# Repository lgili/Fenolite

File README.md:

# Fenolite

**PCB automation in Python, for engineers and AI agents.**

Create PCB projects from code, inspect KiCad and Altium files, and review designs in your browser.
Use the Python library or a CLI with structured JSON results, explicit write plans and conversion loss reports.

[**Get started**](https://github.com/lgili/Fenolite/blob/main/docs/quickstart.md) ·
[Documentation](https://github.com/lgili/Fenolite/blob/main/docs/index.md) ·
[Examples](https://github.com/lgili/Fenolite/tree/main/examples) ·
[What's in 0.5](https://github.com/lgili/Fenolite/blob/main/docs/launch/v0.5.md) ·
[Get help](https://github.com/lgili/Fenolite/issues)

*Actual Fenolite viewer, using a small example authored for this project. No KiCad or Altium installation is needed to view it.*

## Install

Requires **Python 3.11+**. It installs no other package. Heavier features are optional extras.

```bash
python -m pip install fenolite
fenolite capabilities --brief --json
fenolite init blink --confirm --json
fenolite build blink/design.py --out blink/build --confirm --json
fenolite view blink/build --serve
```

Open the local address printed by the viewer. You now have a PCB and a schematic built from
`blink/design.py`, using the built-in component catalog. No external CAD libraries are needed.
These commands create a new `blink` folder; use a fresh location.

This starter is a header, resistor and LED. It is an educational example; choose parts, ratings,
placement and rules for your own circuit before manufacturing. For reviewed write plans, a standalone
HTML export and routing, follow the [quickstart](https://github.com/lgili/Fenolite/blob/main/docs/quickstart.md).

## Three ways to use Fenolite

### Review a design in your browser

Open a KiCad or Altium project, board, schematic or library. Explore layers, highlight nets,
measure geometry and navigate between documents. Export a standalone HTML page for review.

```bash
fenolite view board.kicad_pcb --serve
fenolite view Project.PrjPcb --export review.html --confirm --json
```

The animation uses Fenolite's authored Altium Blink fixture. See the
[viewer guide](https://github.com/lgili/Fenolite/blob/main/docs/viewer.md) for supported items,
3D prerequisites and rendering limits.

### Build from Python

Define components, connections, placement and copper in a versioned source file. Build a project
that can also be opened in its CAD editor. Preserve board edits on rebuild and sync placements back to source.

```python
from fenolite.dsl import Design, Net, Part, connect, mm

design = Design("led")
design.board(mm(30), mm(20))
r1 = Part("R1", "Fenolite:Resistor", footprint="Fenolite:Chip_0603", value="330")
d1 = Part("D1", "Fenolite:LED", footprint="Fenolite:Chip_0603", value="LED")
design.add(r1, d1)
connect(Net("LED_A"), r1[2], d1[1])
r1.place(mm(10), mm(10))
d1.place(mm(20), mm(10))
```

This small fragment illustrates the DSL, not a complete powered circuit. Start with the complete
[starter tutorial](https://github.com/lgili/Fenolite/blob/main/docs/quickstart.md), then explore
[authored examples](https://github.com/lgili/Fenolite/tree/main/examples) and the
[Python DSL](https://github.com/lgili/Fenolite/blob/main/docs/dsl.md).

KiCad's CLI provides ERC, DRC, zone fills and fabrication exports. Production routing uses an external
router or copper declared in the script. The built-in `direct` router is for simple demonstrations.

### Convert and compare projects

Convert between KiCad and Altium, or write a KiCad 10 project for KiCad 9. Review what was kept,
changed or lost, with a readback comparison against the source.

```bash
fenolite convert board.PcbDoc --to kicad --out converted --dry-run --json
fenolite equivalent before.kicad_pcb after.kicad_pcb --level 5 --json
```

**Conversions and Altium writes are experimental in 0.7.** Lossy conversion requires explicit consent.
Support depends on the constructs in the input; review the report and the resulting design.
Read the [conversion guide](https://github.com/lgili/Fenolite/blob/main/docs/conversion.md).

## For AI agents

The same commands return structured JSON, typed errors, evidence labels and file receipts.
A write can be previewed with `--dry-run`, then confirmed using its `--plan` identifier.

```bash
fenolite guide start --text
fenolite skill install --help
```

The package includes an agent guide and board-design practice pages. Agents can inspect parts,
query nets and geometry, build, route, check and export using the same CLI as an engineer.
See the [agent guide](https://github.com/lgili/Fenolite/blob/main/src/fenolite/agent/skill/SKILL.md)
and [CLI contract](https://github.com/lgili/Fenolite/blob/main/docs/cli-contract.md).

<details>
<summary>Full build → fabrication command loop (requires KiCad CLI)</summary>

Use a fresh folder for this complete loop. The first six lines need no external CAD tool; fill,
check, export and render require KiCad's CLI. The direct router is a demonstration router.

```fenolite-loop
fenolite capabilities --brief --json
fenolite init blink --confirm --json
fenolite build blink/design.py --out blink/build --dry-run --json
fenolite build blink/design.py --out blink/build --confirm --json
fenolite place blink/build --strategy grid --confirm --json
fenolite route blink/build --router direct --confirm --json
fenolite fill blink/build --confirm --json
fenolite check blink/build --json
fenolite export blink/build -o blink/fab --all --manifest --confirm --json
fenolite render blink/build -o blink/views --svg --png --confirm --json
```

For fabrication exports, BOM and placement tables, see [exports](https://github.com/lgili/Fenolite/blob/main/docs/exports.md)
and [assembly](https://github.com/lgili/Fenolite/blob/main/docs/assembly.md).

</details>

## Support at a glance

> **Status: version 0.7.** Python scripts build KiCad 9/10 PCB and schematic projects. The agent loop
> uses KiCad's ERC/DRC checks, the board engineering analyses and an MCP server; conversion supports
> KiCad/Altium and the older KiCad major. Altium writes, computed Altium pours and conversions are
> experimental. See the [release scope and limits](https://github.com/lgili/Fenolite/blob/main/docs/release/v0.7.md).

| Workflow | What you need | Status in 0.7 |
|---|---|---|
| Build the starter; inspect and view supported files | Python 3.11+, browser for the viewer | Shipped; format-specific rendering limits apply |
| KiCad project generation | Python; KiCad 9 or 10 to open in the editor | Shipped |
| KiCad ERC, DRC, fill and fabrication export | `kicad-cli` 9 or 10 | Shipped; engineering review still required |
| External routing | A supported router and its prerequisites | Freerouting and KiCadRoutingTools integrations |
| KiCad/Altium conversion and KiCad downgrade | Requirements vary by direction | Experimental; explicit loss report |
| Altium project generation | Python; Altium for native validation | Experimental |

Linux, macOS and Windows are supported. Optional extras include `geo` for polygon operations
and `kicad-ipc` for a live KiCad session. Since 0.6 the package includes the stdlib-only MCP server
(`fenolite mcp`), script editing and image replies described in the
[MCP documentation](https://github.com/lgili/Fenolite/blob/main/docs/mcp.md). See
[installation and prerequisites](https://github.com/lgili/Fenolite/blob/main/docs/quickstart.md).

The viewer, conversion, board panels, slots and review tools ship since 0.5; 0.6 adds the MCP server, the
board engineering tools (analyses, tidy, reuse, silkscreen, test points, DRC gates) and the Python API.
0.7 carries Altium boards through KiCad and back (rules, classes, planes, unions, fonts, computed pours), still
experimental.
Native Draftsman writing and Embedded Board Arrays remain gated. Detailed scope and deferred checks are in the
[release record](https://github.com/lgili/Fenolite/blob/main/docs/release/v0.7.md).

## Help and contribute

Trying Fenolite on a public or self-authored example? Tell us what worked and where you got stuck.
[Ask a question or report a bug](https://github.com/lgili/Fenolite/issues), including the version,
command and error output. Keep private designs and personal paths out of public reports.

For development, clone [the repository](https://github.com/lgili/Fenolite), run `uv sync --extra dev`
and read [CONTRIBUTING.md](https://github.com/lgili/Fenolite/blob/main/CONTRIBUTING.md).

## License

[Apache-2.0](https://github.com/lgili/Fenolite/blob/main/LICENSE).
Format knowledge comes from public sources under the project's
[clean-room rules](https://github.com/lgili/Fenolite/blob/main/LEGAL.md).
Results carry evidence labels; detailed claims live in the
[evidence matrix](https://github.com/lgili/Fenolite/blob/main/docs/evidence/matrix.md).

*Fenolite* is Portuguese for phenolic board material, the laminate many of us etched our first boards on.

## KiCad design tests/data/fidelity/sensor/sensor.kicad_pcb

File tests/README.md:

# tests

| Folder | What lives there | Needs |
|---|---|---|
| `unit/` | fast, hermetic tests of `fenolite` and of repository invariants | nothing |
| `consistency/` | CLI contract checks run against every registered command (change c0002) | nothing |
| `residue/` | IP residue scan over the tree and the built wheel (change c0003) | nothing; private token list optional |
| `corpus/` | tests over the fetched public corpus (`tools/corpus_fetch.py`) | `needs_corpus` |
| `kicad/` | tests that call `kicad-cli` 9.0/10.0 | `needs_kicad` |
| `libs/` | census of the official KiCad libraries (read, resolve, count; nothing committed) | `needs_libs`, `slow` |
| `data/` | small fixtures authored for Fenolite, declared in `data/MANIFEST.toml` | nothing |

Run everything that needs no external tool with `uv run pytest -q`. `make check-fast` runs the
checks and the tests of `unit/`, `residue/` and `consistency/` that need no external resource;
`make check` runs every test. Both use parallel workers (see "Parallel runs" below).

## Markers and modes

| Marker or variable | Effect |
|---|---|
| `needs_kicad`, `needs_corpus`, `needs_libs` | skip when the resource is absent |
| `FENOLITE_REQUIRE=kicad,corpus,libs` | required-resource mode: those skips become failures (CI oracle jobs) |
| `kicad_min_major(10)` | skip when the running `kicad-cli` is older (for example `pcb upgrade`, 10.0 only); never a failure, even in required-resource mode |
| `FENOLITE_HEAVY=1` | include corpus files over 20 MB |
| `FENOLITE_KICAD_CLI=/path` | use this `kicad-cli` (a missing file counts as no `kicad-cli`) |
| `KICAD10_FOOTPRINT_DIR`, `KICAD10_SYMBOL_DIR` (or `KICAD9_*`) | official library folders for `needs_libs`; they take precedence over the install |
| `FENOLITE_KICAD_INSTALL_DIR=/path` | the KiCad share folder to use instead of the default install (a missing path counts as no install) |
| `FENOLITE_CENSUS_OUT=/path/census.json` | where `tests/libs/` writes its counts (never a tracked file) |
| `FENOLITE_ALTIUM_REPOUR_DIR=/path` | the folder of a Repour run (`tools/kit_pour_c0463.py`); without it the tests of `test_altium_pour_repour_c0463.py` that need Altium's saved boards skip |

## Parallel runs

`make check`, `make check-fast` and the CI jobs run the tests on `pytest-xdist` workers
(capability ci-baseline, "Parallel test runs"). A plain `uv run pytest ...` stays serial.

| Where | Options |
|---|---|
| `make check`, `make check-fast` | `-n auto --maxprocesses 8 --dist loadfile` (`PYTEST_WORKERS`, `PYTEST_MAX_WORKERS`, `PYTEST_PARALLEL`) |
| CI `unit`, `kicad-10`, `kicad-9` | `-n auto --dist loadfile` (4 workers on the Linux runners, 3 on macOS) |
| by hand | `uv run pytest tests/kicad -q -n 8 --dist loadfile` |

Rules for tests:

- Write only below `tmp_path`. Use no fixed port and no fixed path outside the repository.
- Do not depend on a test of another file. A summary test may read what the earlier tests of its
  own file collected: `--dist loadfile` runs a file on one worker, in file order. `--dist load`
  breaks such files, so do not use it.
- Give every subprocess call that must finish a limit of 10 s or more. A short limit is only for
  a call that must time out.
- The write modes are serial. With `FENOLITE_PROBES_WRITE=1`, `FENOLITE_GOLDEN_WRITE=1`,
  `FENOLITE_CENSUS_OUT` or `FENOLITE_CHECK_EVIDENCE` set, a run with `-n` stops with a usage error
  (exit code 4): several workers would write the same file.
- Prove a change of the options with `uv run python tools/test_outcomes.py serial.xml parallel.xml`
  on the `--junitxml` files of a serial and a parallel run.

### Measurements (2026-10-04, change c0049)

Machine: 10 cores (4 performance, 6 efficiency), macOS, KiCad 10.0.6, corpus and library caches
present. The machine was never quiet: other agents ran test suites and a Docker container during
every run below (2 to 12 other pytest processes, load average 5 to 38). The times are therefore
upper bounds, and comparisons between rows are rough.

| Run | Options | Wall time | Outcomes |
|---|---|---|---|
| whole suite, before | serial | 3357 s (56 min) | 4827 passed, 24 skipped |
| `tests/kicad` | serial (part of the run above) | 1783 s | 584 passed, 10 skipped |
| `tests/kicad` | `-n 6 --dist loadfile` | 605 s | 584 passed, 10 skipped |
| `tests/kicad` | `-n 8 --dist loadfile` | 546 s | 584 passed, 10 skipped |
| `tests/kicad` | `-n 10 --dist loadfile` | 617 s | 584 passed, 10 skipped |
| `tests/kicad` | `-n 8 --dist load` | 838 s | 583 passed, 11 skipped: `test_upgraded_summary` lost the results of its file |
| `make check-fast` | `-n auto --maxprocesses 8 --dist loadfile` | 122 s (tests 101 s) | 3832 passed, 6 skipped |
| `make check`, after (rebased: 736 more tests) | `-n auto --maxprocesses 8 --dist loadfile` | 1226 s (20 min; tests 1205 s) | 5563 passed, 24 skipped |

- The cap is 8: the fastest of 6, 8 and 10, and it leaves two cores to the `kicad-cli` threads.
- With `loadfile` the longest file bounds the run. In the `tests/kicad` runs with 8 and 10 workers,
  `tests/kicad/check/test_corpus_rt.py` alone took 509 s and 611 s on its worker (412 s serial). The
  next ones are `tests/libs/test_official_resolve.py` (468 s serial), `tests/libs/test_official_read.py`
  (411 s) and `tests/kicad/check/test_check_demos.py` (364 s). Splitting them is later work.
- Equality. `tools/test_outcomes.py` on the serial and the final parallel JUnit files: the 4849
  test ids present in both runs have the same outcome (0 differences). The parallel run has 738
  more ids (723 from changes merged between the two runs, 15 from this change) and lacks 2 that
  were renamed. On one commit, the 594 ids of `tests/kicad` (`-n 8 --dist loadfile`) equal the
  serial run id by id.
- Before and after are not the same suite: the final run holds 15 % more tests and used 4538 s of
  CPU against 3064 s. Per test, the wall time went from 0.69 s to 0.22 s (3.2 times faster) while
  other agents kept the machine at a load average of 18 to 31.
- The maintainer's earlier figure for a serial `make check` on a quiet machine was 11 minutes.

### CI effect (2026-10-04, change c0049)

The first run with the parallel steps is https://github.com/lgili/Fenolite/actions/runs/37178050484
(commit 87c4244). The last serial run that finished on `main` is https://github.com/lgili/Fenolite/actions/runs/37171749778
(commit 75f3a87); three changes landed between the two, so the suites are not the same.

| Job | Serial: job, pytest | Parallel: job, pytest | Serial outcomes | Parallel outcomes |
|---|---|---|---|---|
| `unit` (ubuntu) | 139 s, 115.82 s | 108 s, 84.14 s | 4304 passed, 1080 skipped | 4490 passed, 1109 skipped |
| `unit` (macos) | 246 s, 201.36 s | 81 s, 56.46 s | 4304 passed, 1080 skipped | 4490 passed, 1109 skipped |
| `kicad-9` | 242 s, 208.50 s | 274 s, 239.96 s | 388 passed, 340 skipped, 1 xfailed | 426 passed, 343 skipped, 1 xfailed |
| `kicad-10` | 1485 s, 1440.18 s | 1088 s, 1051.89 s | 1140 passed, 21 skipped | 1182 passed, 21 skipped |
| whole run | 1492 s (24 min 52 s) | 1095 s (18 min 15 s) | all jobs passed | all jobs passed |

- Totals. Each job grew by exactly the tests added between the two commits, counted with
  `--collect-only` on both trees: 215 for the whole suite (`unit`, 5384 to 5599), 42 for
  `tests/kicad tests/corpus` (`kicad-10`, 1161 to 1203) and 41 for `tests/kicad` (`kicad-9`, 729 to
  770). No test failed in either run.
- `kicad-9` lists every outcome (`-rA`): the 386 passed and xfailed test ids that both logs list
  have the same outcome, and the 38 ids only in the parallel log are the tests of
  `tests/kicad/copper`, added after the serial run.
- Times. `kicad-10` bounds the run: its pytest step went from 24 min 0 s to 17 min 32 s with 42 more
  tests. The design expected a drop to about a third; `--dist loadfile` is bounded by its longest
  file (see the measurements above). `kicad-9` did not get faster: 31 s more with 41 more tests.

## Audited CI partitions (c0380)

[CI profiles](../docs/ci.md) retain all five unit environments, both KiCad majors and required heavy
corpus tests at the full gate. KiCad 10 runs four whole-file partitions on separate runners. Each
partition collects the complete baseline, validates the selected execution collection and records a
terminal outcome for every selected node id. The full audit requires all fourteen receipts on the
same commit, with an exhaustive disjoint union per suite. Missing artifacts are failures, not skips.

`tools/ci_tests.py run` retains `--dist loadfile`; it does not make within-file dependencies safe for
another scheduler. Timing/JUnit artifacts show where collection, setup and test execution cost time.
`tools/test_outcomes.py` still compares legacy JUnit outcomes. The authored serial/xdist and partition
controls are `tests/unit/test_ci_execution.py`; no corpus payload is copied into those controls.
Historical timings and the pending exact-head proof are documented in `docs/ci.md`.

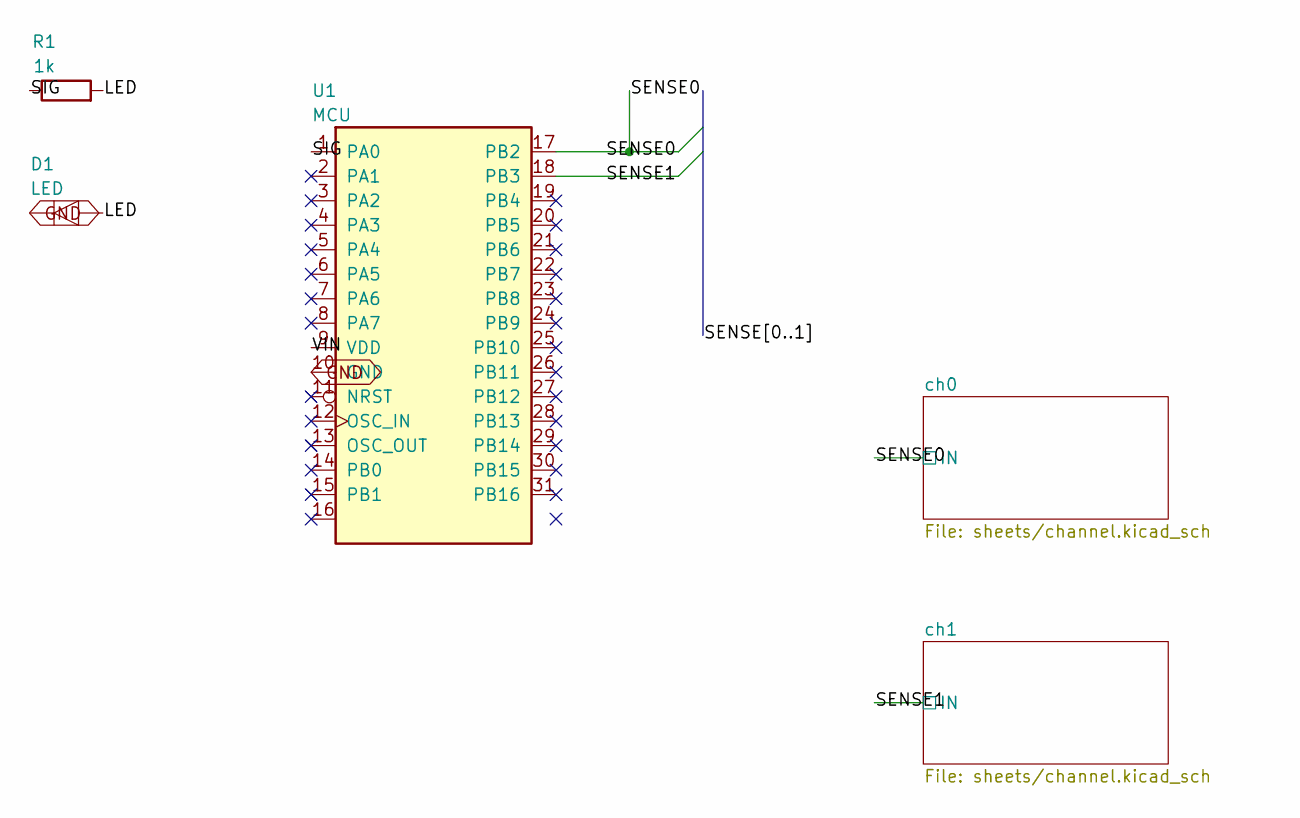
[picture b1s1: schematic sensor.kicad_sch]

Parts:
D1: LED; Mini_LED_THT_3mm
R1: 1k; Mini_R_0603
U1: MCU; Mini_QFP-32_7x7mm_P0.8mm

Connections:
GND: D1.1 (K), U1.10 (GND); also elsewhere on the board
LED: D1.2 (A), R1.2
SENSE0: U1.17 (PB2); also elsewhere on the board
SENSE1: U1.18 (PB3); also elsewhere on the board
SIG: R1.1, U1.1 (PA0)
VIN: U1.9 (VDD)

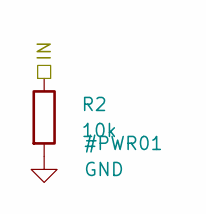
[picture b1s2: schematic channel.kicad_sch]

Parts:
R2: 10k; Mini_R_0603

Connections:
GND: R2.2; also elsewhere on the board
SENSE0: R2.1; also elsewhere on the board

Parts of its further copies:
R3: 10k; Mini_R_0603

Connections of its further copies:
GND: R3.2; also elsewhere on the board
SENSE1: R3.1; also elsewhere on the board

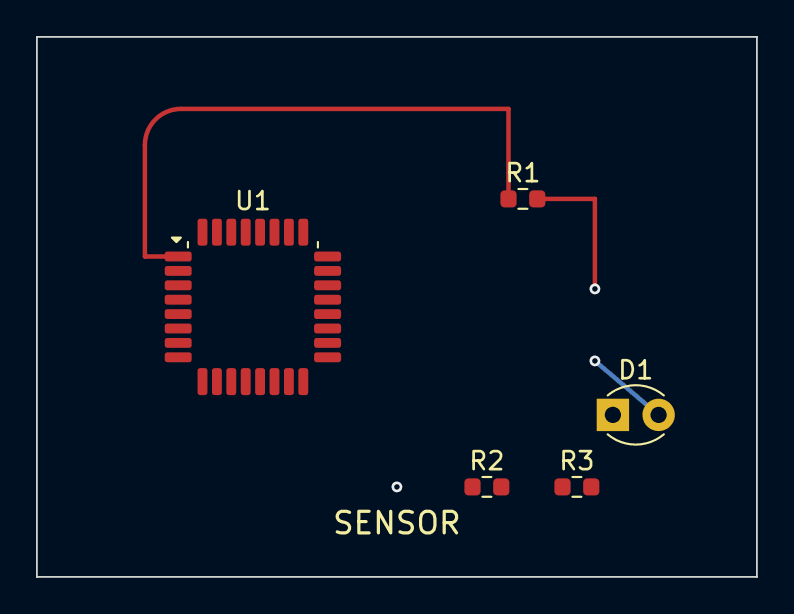
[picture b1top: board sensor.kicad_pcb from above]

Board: 4 copper layers, 40.0 x 30.0 mm, 5 parts (0 on the bottom side), 5 nets.

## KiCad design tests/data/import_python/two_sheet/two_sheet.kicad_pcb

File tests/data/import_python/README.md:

# import_python

Authored for Fenolite: the inputs of the `fenolite import` tests (change c0275).

- `src/two_sheet.py`: the authored design script, with the project tables that name the authored mini
  library of `tests/data/libs`.
- `two_sheet/`: its build for KiCad 10 (`fenolite build two_sheet.py --out ../two_sheet --confirm
  --timestamp 2026-10-30T00:00:00Z` in `src/`), the one committed input; `tests/unit/importer/test_data.py`
  keeps it equal to a fresh build.

The other boards of the tests (no schematic, a `group`, an edited instance, an old format version, no
`fenolite.path`, KiCad sheet names) are made from this board by `tests/_importcode.py` in each test's
temporary folder. No board, value or name here comes from any other project.

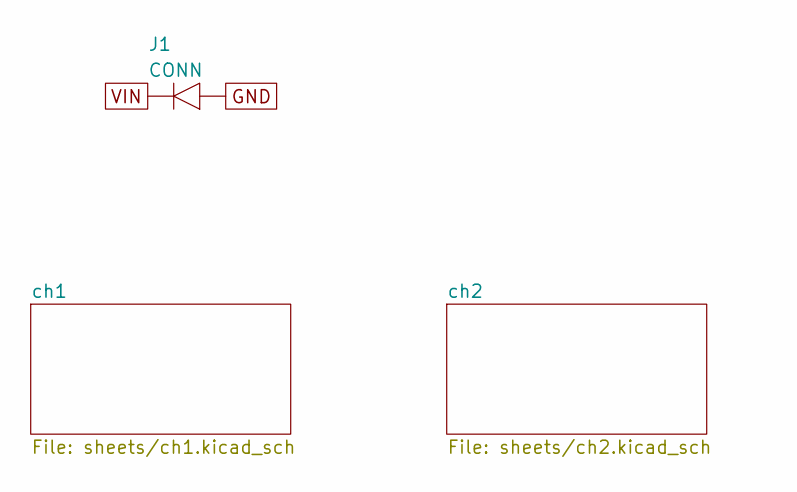
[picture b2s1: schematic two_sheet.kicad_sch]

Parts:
J1: CONN; Mini_LED_THT_3mm

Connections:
GND: J1.2 (A); also elsewhere on the board
VIN: J1.1 (K); also elsewhere on the board

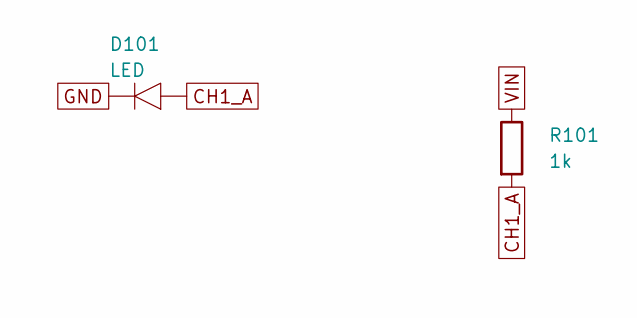
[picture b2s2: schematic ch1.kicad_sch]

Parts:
D101: LED; Mini_LED_THT_3mm
R101: 1k; Mini_R_0603

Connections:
CH1_A: D101.2 (A), R101.2
GND: D101.1 (K); also elsewhere on the board
VIN: R101.1; also elsewhere on the board

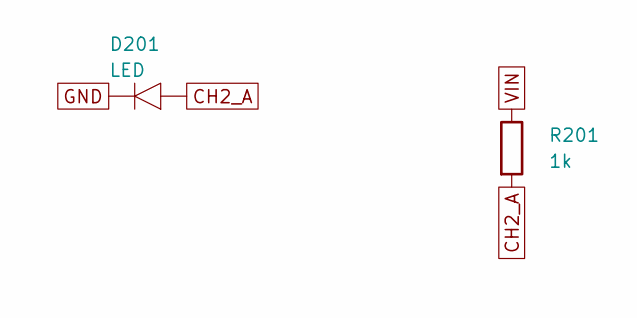
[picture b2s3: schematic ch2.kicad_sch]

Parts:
D201: LED; Mini_LED_THT_3mm
R201: 1k; Mini_R_0603

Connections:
CH2_A: D201.2 (A), R201.2
GND: D201.1 (K); also elsewhere on the board
VIN: R201.1; also elsewhere on the board

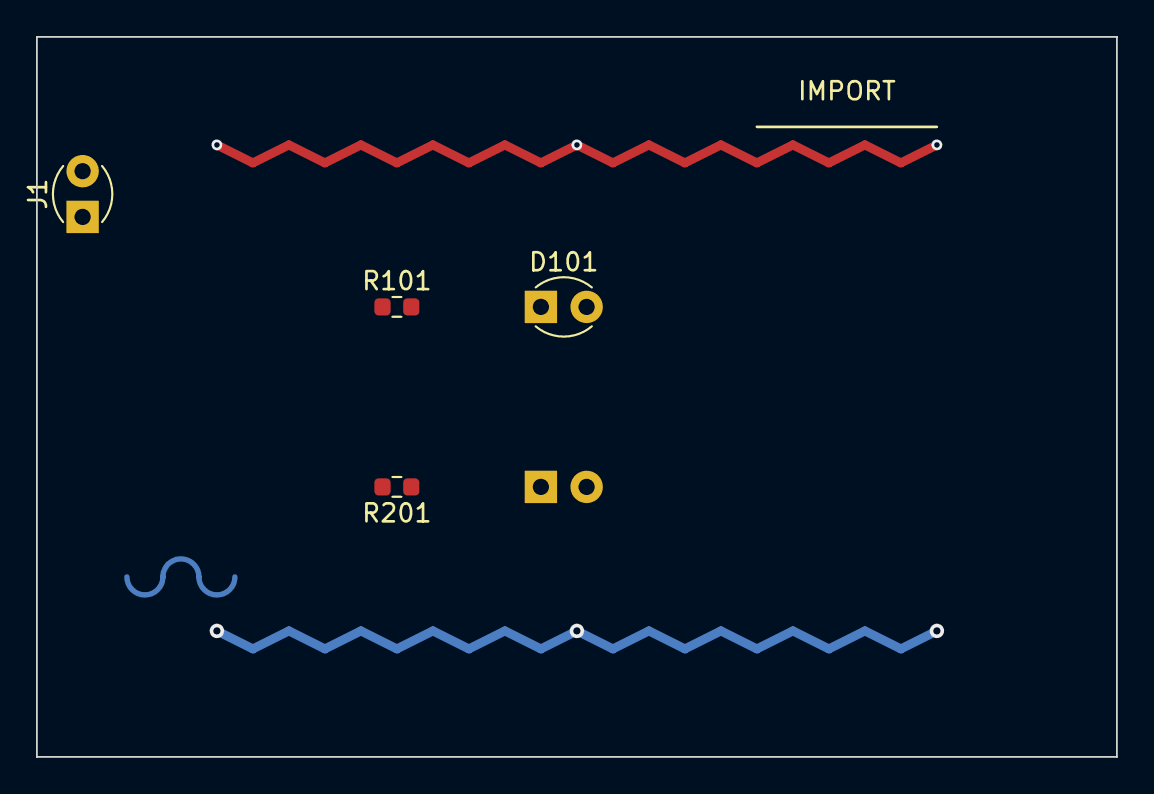
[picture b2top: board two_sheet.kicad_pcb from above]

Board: 2 copper layers, 60.0 x 40.0 mm, 5 parts (1 on the bottom side), 4 nets.

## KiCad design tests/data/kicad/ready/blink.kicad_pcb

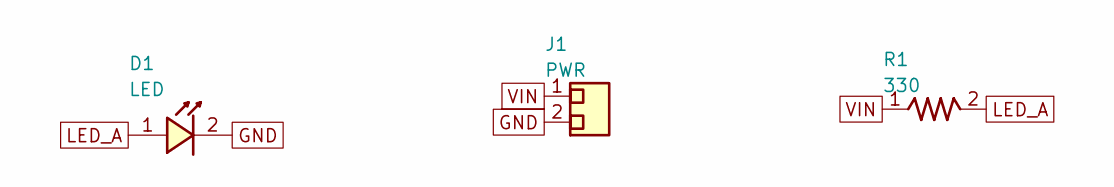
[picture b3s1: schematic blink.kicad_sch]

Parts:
D1: LED; Chip_0603
J1: PWR; Header_1x2_P2.54
R1: 330; Chip_0603

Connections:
GND: D1.2 (K), J1.2
LED_A: D1.1 (A), R1.2 (B)
VIN: J1.1, R1.1 (A)

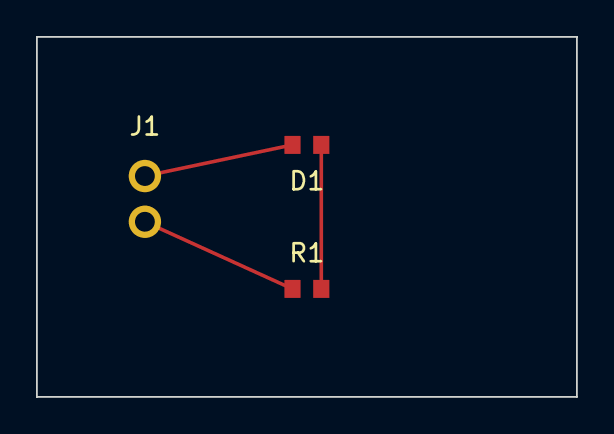
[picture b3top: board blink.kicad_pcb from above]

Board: 2 copper layers, 30.0 x 20.0 mm, 3 parts (0 on the bottom side), 3 nets.

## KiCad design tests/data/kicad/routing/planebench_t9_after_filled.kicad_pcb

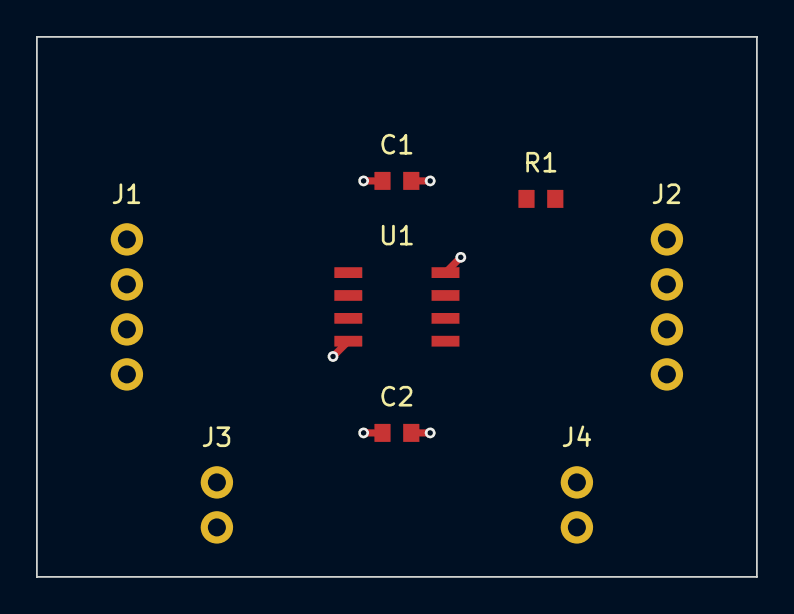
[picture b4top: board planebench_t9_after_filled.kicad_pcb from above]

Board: 4 copper layers, 40.0 x 30.0 mm, 8 parts (0 on the bottom side), 10 nets.

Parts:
C1, C2: 100n; Chip_0603
J1: IN; Header_1x4_P2.5
J2: OUT; Header_1x4_P2.5
J3, J4: HV; Header_1x2_P2.5
R1: 1k; Chip_0603
U1: MCU; SOIC_8

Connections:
GND: C1.2, C2.2, J1.2, J2.3, U1.4
HV1: J3.1, J4.1
HV2: J3.2, J4.2
SIG1: J1.3, U1.1
SIG2: J1.4, U1.2
SIG3: R1.1, U1.3
SIG4: R1.2, U1.5
SIG5: J2.1, U1.6
SIG6: J2.2, U1.7
VCC: C1.1, C2.1, J1.1, J2.4, U1.8

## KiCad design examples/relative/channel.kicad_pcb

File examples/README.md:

# examples

Designs authored for Fenolite (CC0-1.0), used as documentation and as end-to-end tests. Every
example is original work: no file, value, name or layout comes from any organisation's projects.

| example | what it shows |
|---|---|
| `blink_2layer/` | the thin DSL: a mini MCU, a resistor and an LED (bottom side) on a 50 mm × 30 mm two-layer board, from the authored mini library through the folder's own library tables; `fenolite build` turns it into a KiCad 9.0 or 10.0 project: the board, project and rules files, the schematic `blink.kicad_sch` with `sym-lib-table`, and under `lib/` the three footprints and the symbol libraries `Mini.kicad_sym` and `fenolite.kicad_sym` (`docs/schematic.md`); the 29 pins the circuit does not use are marked with `no_connect`, so KiCad's ERC reports nothing on the built project |
| `blink_routed/` | the blink with copper declared by the script: three tracks from pad to pad with waypoints and layer-changing vias, and a row of stitching vias, 11 tracks and 7 vias in all; the build resolves them after placement, so a part moved in KiCad pulls its tracks along (`docs/copper.md`) |
| `board_40parts/` | forty parts in two modules: two mini MCUs, each driving nine LEDs through nine resistors, with an enable pull-up, on a 100 mm × 80 mm two-layer board with a `GND` zone on both layers and one scripted ground via under each controller; only the two controllers are placed (and locked), the rest is left to `fenolite place --strategy grid`; the board minimums come from `design.rules.minimum`, so KiCad's DRC judges the finished board against the script's own rules; it is the second board of the v0.1 acceptance loop (`docs/release/v0.1.md`); its schematic takes one A3 sheet, a row of symbols per module, and KiCad's ERC and parity test report nothing on it |
| `board_coverage/` | one of each board item of change c0277 on the blink circuit, on a four-layer board: a knockout text and a `GND` heat spreader on copper, user layers, a radial dimension, a leader and a centre mark, a zone outline with an arc, a placement rule area, a group, a board image read from `logo.png` (an authored checkerboard), teardrops on the power class and on one via, a free via, a part not populated, a footprint with a trapezoid, a chamfered, a rounded and a custom pad, the overrides and an edited pad of one instance, a bold reference, a 3D model named by the script, and two verbatim items; an Altium build writes what its records hold and names every other item, and refuses the footprint of the shaped pads |
| `catalog/` | a 5 V to 3.3 V linear supply with an indicator LED from the built-in catalog alone (`Fenolite:` lib ids, no library table); its build is recorded in `tests/data/catalog/golden.json`, the guard of the catalog's move from Python tables to record files (change c0259) |
| `devices/` | parts placed from device records (change c0248, `docs/devices.md`): a 5 V to 3.3 V step-down board whose regulator `U1` comes from `devices/example_buck.toml` beside the script (an illustrative device, not a real product: an authored symbol, a catalog footprint, the map from pin function to pad, ratings and the label `UNVERIFIED`), and whose passives, LED and connector come from the shipped generic `Fenolite:` devices; pins are named by function (`u1.VIN`), and the build reports each device in `result.devices` |
| `sensor_rails/` | interface parameters (change c0252, `docs/dsl.md`, "Rails, grounds and logic"): a 12 V input, the block `buck` whose port `VOUT` promises 3.3 V ± 3 % at 1 A, an MCU and an I2C sensor whose illustrative device records in `devices/` declare their power, I2C and logic ports with operating values and thresholds; whole interfaces are joined with `connect(bus, mcu.i2c1, sen.i2c)`, and the stage `circuit.rules` judges the rails, the levels and the pull-ups. `good.py` passes; `bad.py` adds a 1.1 A fan that overloads `3V3` and pulls the bus up to `V12`, so its build stops with `circuit.rail-current`. Both share `rails/board.py`, and `good.lock` holds the refs |
| `pins/` | pin assignment at the interface level (change c0257, `docs/pins.md`): an MCU whose illustrative record in `devices/` offers its I2C, UART, SPI and ADC on several pin sets, an I2C sensor and a debug header; the script takes `mcu.take(I2C)` and `mcu.take(UART, option="UART2", name="debug")`, and the build chooses the pins, lists them in `result.pins` and records them in the `[pins]` section of the committed `design.lock` |
| `blink_official/` | the same circuit on KiCad's official libraries; DSL source only, built by a `needs_libs` test into a temporary folder |
| `altium_sample/` | the experimental Altium target (`fenolite build … --target altium`): eight parts at the top level and in two modules, a 5 V regulator, a driver with an enable pull-up and an LED, two supplies sharing `GND`, every pin connected by number; its lib ids name `FenoliteSample.SchLib` and `FenoliteSample.PcbLib`, which Fenolite does not ship; the built files are committed under `tests/data/altium/sample/` |
| `altium_kicad/` | the Altium target from KiCad symbols (change c0034): a dual amplifier with common supply pins, a controller with pins on four sides, upright resistors and a connector from the authored CC0 `FenoliteDemo.kicad_sym`, found through the folder's `sym-lib-table`; the build writes their pins and units into `altium_kicad.SchLib`, and the built files are committed under `tests/data/altium/kicad_example/` |
| `altium_hier/` | sheets per module and a signal harness for the Altium target (change c0037, `--altium-sheets modules`): a connector on the top sheet, a controller and a flash memory in two modules, an `SPI` harness between them; `partial.py` adds a harness entry whose net stays on one sheet; the lib ids name `FenoliteHier.SchLib` and `FenoliteHier.PcbLib`, which Fenolite does not ship; the built files are committed under `tests/data/altium/hier/` |
| `altium_hier_board/` | the blink circuit of `blink_2layer/` split into the modules `driver` and `led`, with its board and the same authored libraries, so the Altium build writes a PCB document whose parts link through their sheet symbols |
| `generated/` | footprints generated from package records (change c0260, `docs/footprint-generators.md`): one record of each family in `packages/` beside the script (a 0603 chip, a SOD-123 diode, a SOIC-8, a QFN-16 with exposed pad, a 12-ball grid array, a TO-220, a DIP-8, a 1x2 pin header and a 3-position connector of a series), each with the numbers of a cited public outline and, when the source gives one, the manufacturer's land; `Footprint.from_package` draws them under `drawing/1`, the build writes `lib/Local.pretty/` and the STEP models of the eight footprints with bodies under `lib/Local.3dshapes/`, and `fenolite library generate examples/generated/packages/*.toml --out lib` writes the same files and `lib/Local.PcbLib` without a design |
| `symbols/` | symbols generated from pin tables (change c0261, `docs/symbols.md`): the illustrative regulator `pins/EXB6202.toml` (one unit, an exposed pad stacked on `GND`, one variant) and the illustrative 120-pin controller `pins/EXM120.toml` (split into two signal units and a named power unit, with alternates and one variant); `design.py` generates both with `Symbol.from_pins`, places the regulator through its variant and writes all four symbols into `lib/Example.kicad_sym`; `tests/kicad/library/test_symbol_generate_oracle.py` loads the library in `kicad-cli` |
| `import_python/` | the code `fenolite import` writes from a board authored for Fenolite (`tests/data/import_python/two_sheet`, changes c0275/c0276; `docs/import.md`): `design.py` with the board, nets, the class `Power`, five parts in two modules with their keys, connections, placements, a zone, a keep-out and drawings; `copper.py` with the copper as `track_table`, `arc_table` and `via_table` rows; retained `schematic.toml` and native source symbols in `lib/`, `design.lock` and `PROVENANCE.json`; each `.py` file is marked `Authored for Fenolite` after its provenance header |
| `kit/` | the five sample scripts of the Altium verification kit (`docs/altium-kit.md`): `flat`, `tree`, `routed`, `board6` and `libs`, all on Fenolite's own catalog; `fenolite kit build` builds them into the kit, and nothing it builds is committed |
| `lock/` | the design lock (change c0249): a regulator and an indicator LED in two modules, most parts written without a ref (`reg.part(lib_id=...)` gives the path `reg/U`, `name=` gives `reg/c_in`) and one explicit `J1`; the build assigns the refs per prefix in natural path order and records them in the committed `design.lock`, which a release build checks with `fenolite build ... --frozen`; every symbol and footprint comes from Fenolite's catalog |
| `picks/` | parts chosen by parameters (change c0254, `docs/picking.md`): `design.py` asks an input capacitor by value, rating and dielectric (picked from the illustrative project family `devices/caps.toml`), a feedback divider in the block `buck1` (`voltage_divider`), an RC filter, an LED resistor and the pull-ups of an I2C bus; `divider.py` holds the divider alone; the build picks every part from the shipped `Fenolite:` families and `devices/`, records each pick in the committed `design.lock` and `divider.lock`, and reports what each generator achieved (`gen.achieved`); `fenolite pick examples/picks` lists the picks |
| `families/` | exact part numbers from ordering-code grammars (change c0263, `docs/picking.md`, "Families with ordering codes"): three illustrative `fenolite.family.v1` grammars of an invented manufacturer, `Example Passive`, in `devices/` (`example_mlcc.toml`, value in `eia3`; `example_chip_r.toml`, `eia4` with an opaque tail; `example_film_r.toml`, `rkm`), and `design.py`, whose capacitor and resistor queries the build turns into exact MPNs with their manufacturer, recorded in the committed `design.lock`; `fenolite family decode EX05C471JBT --project examples/families` reads an MPN back |
| `yardstick/` | the yardstick board, at stage 5 of five (`docs/evidence/yardstick.md`): an invented controller of eight identical 48 V buck channels with an isolated high-voltage sense section, 388 parts of KiCad's official libraries and of the generated hole and assembly libraries on a 250 mm × 110 mm six-layer board with a declared stack-up, inner planes, slots under the isolators, plated mounting holes with keep-outs, a high-voltage rule area, the USB pair's rules and impedance target, thermal via arrays, placement rules, a net tie, fiducials, tooling holes and test points; one function makes a channel and is called eight times, references are `n·100 + k`, the script places every part and draws no track, and every value is stated once at the top as `chosen for the example` or with a source id; DSL source only, built for KiCad 10 from the verified library cache by a `needs_libs` test and taken through the loop every night by `tools/yardstick.py run` (routed by Freerouting, judged by KiCad), with a time and memory budget per step |

| `routing/` | the fixed-seed router acceptance boards of change c0370: `acceptance.py` writes a design script of 4 to 160 two-pad catalog passives on a grid, on a two- or four-layer board, with signal nets paired inside blocks of eight cells in a seeded order and pads 2 on the supply `VIN`/`GND` (a `GND` zone on `B.Cu`, or `GND` on `In1.Cu` and `VIN` on `In2.Cu`); its own SplitMix64 mixer makes the same arguments give the same bytes on every Python version, pinned by `tests/unit/routing/test_completion_fixtures.py`; nothing is committed but the generator |
| `library-devices/` | one illustrative device and its symbol/footprint vendored from an authored local release, exact item pins in the lock, built offline with no global CAD tables; see `docs/library-devices.md` |

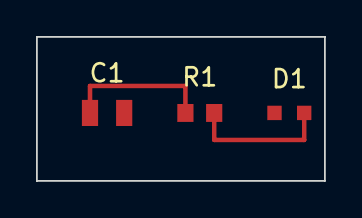
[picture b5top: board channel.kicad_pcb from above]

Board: 2 copper layers, 16.0 x 8.0 mm, 3 parts (0 on the bottom side), 3 nets.

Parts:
C1: 100n; Chip_0805
D1: green; LED0603_Kingbright_APT1608SURCK
R1: 1k; Chip_0603

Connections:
GND: C1.2, D1.1
VIN: C1.1, R1.1
ch/A: D1.2, R1.2
